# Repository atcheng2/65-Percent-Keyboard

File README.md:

# 65-Percent-Keyboard

QMK Based Keyboard based on the ATmega32A and the VUSB protocol. This build
implements an ANSI 65% layout for standard MX-style switches. The ATmega32A is
implemented over the more standard ATmega32u4 that has native USB support due to
budget constraints and part availability.

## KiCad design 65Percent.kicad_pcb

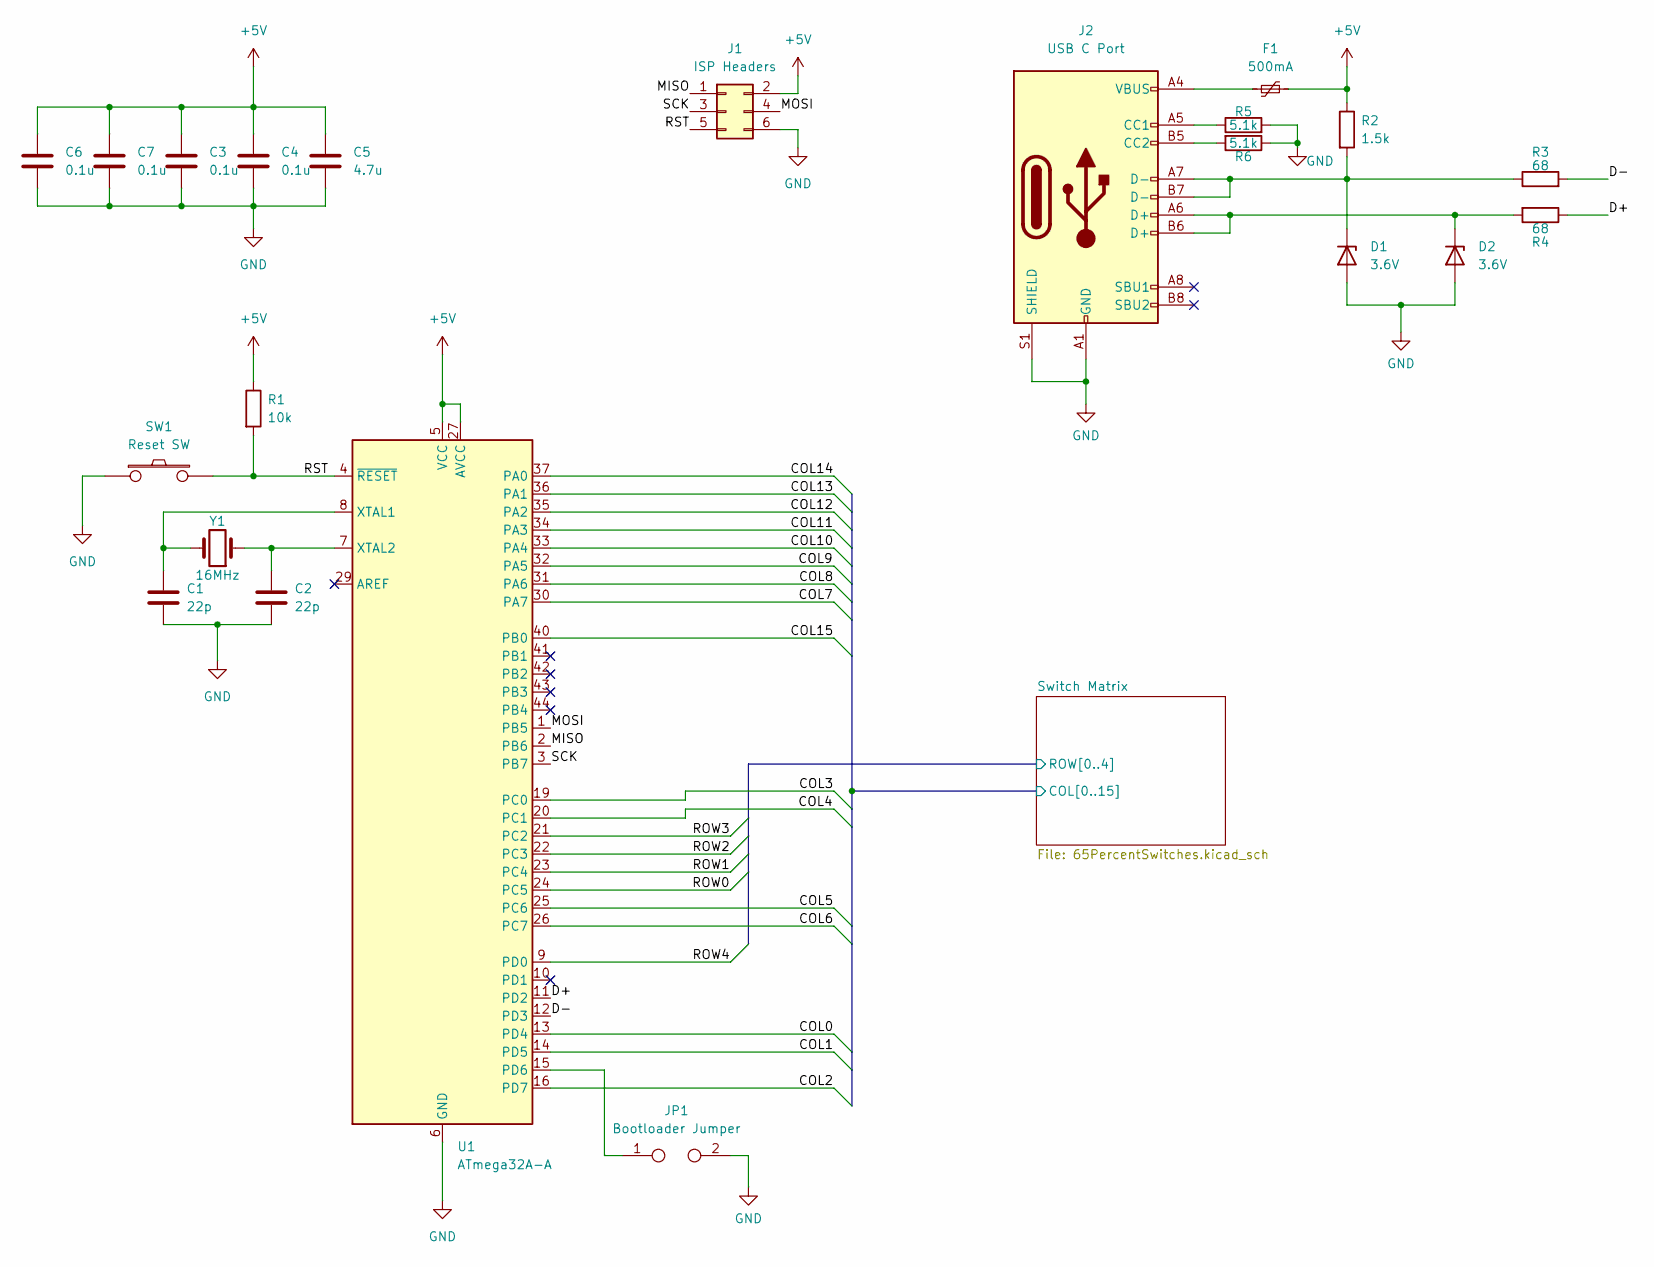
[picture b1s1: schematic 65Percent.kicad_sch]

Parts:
C1, C2: 22p; C_0805_2012Metric_Pad1.18x1.45mm_HandSolder
C3, C4, C6, C7: 0.1u; C_0805_2012Metric_Pad1.18x1.45mm_HandSolder
C5: 4.7u; C_0805_2012Metric_Pad1.18x1.45mm_HandSolder
D1, D2: 3.6V; D_DO-35_SOD27_P7.62mm_Horizontal
F1: 500mA; Fuse_0805_2012Metric_Pad1.15x1.40mm_HandSolder
J1: ISP Headers; PinHeader_2x03_P2.54mm_Vertical
J2: USB C Port; USB_C_2169900002
JP1: Bootloader Jumper; SOLDER_JUMPER_2
R1: 10k; R_0805_2012Metric_Pad1.20x1.40mm_HandSolder
R2: 1.5k; R_0805_2012Metric_Pad1.20x1.40mm_HandSolder
R3, R4: 68; R_0805_2012Metric_Pad1.20x1.40mm_HandSolder
R5, R6: 5.1k; R_0805_2012Metric_Pad1.20x1.40mm_HandSolder
SW1: Reset SW; Pushbutton_PTS526
U1: ATmega32A-A; TQFP-44_10x10mm_P0.8mm
Y1: 16MHz; Clock_THT

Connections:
+5V: C3.1, C4.1, C5.1, C6.1, C7.1, F1.2, J1.2, R1.1, R2.1, U1.5 (VCC), U1.17 (VCC), U1.27 (AVCC), U1.38 (VCC)
/D+: R4.1, U1.11 (PD2)
/D-: R3.2, U1.12 (PD3)
/MISO: J1.1, U1.2 (PB6)
/MOSI: J1.4, U1.1 (PB5)
/RST: J1.5, R1.2, SW1.2, U1.4 (~RESET)
/SCK: J1.3, U1.3 (PB7)
/Switch Matrix/COL0: U1.13 (PD4); also elsewhere on the board
/Switch Matrix/COL1: U1.14 (PD5); also elsewhere on the board
/Switch Matrix/COL2: U1.16 (PD7); also elsewhere on the board
/Switch Matrix/COL3: U1.19 (PC0); also elsewhere on the board
/Switch Matrix/COL4: U1.20 (PC1); also elsewhere on the board
/Switch Matrix/COL5: U1.25 (PC6); also elsewhere on the board
/Switch Matrix/COL6: U1.26 (PC7); also elsewhere on the board
/Switch Matrix/COL7: U1.30 (PA7); also elsewhere on the board
/Switch Matrix/COL8: U1.31 (PA6); also elsewhere on the board
/Switch Matrix/COL9: U1.32 (PA5); also elsewhere on the board
/Switch Matrix/COL10: U1.33 (PA4); also elsewhere on the board
/Switch Matrix/COL11: U1.34 (PA3); also elsewhere on the board
/Switch Matrix/COL12: U1.35 (PA2); also elsewhere on the board
/Switch Matrix/COL13: U1.36 (PA1); also elsewhere on the board
/Switch Matrix/COL14: U1.37 (PA0); also elsewhere on the board
/Switch Matrix/COL15: U1.40 (PB0); also elsewhere on the board
/Switch Matrix/ROW0: U1.24 (PC5); also elsewhere on the board
/Switch Matrix/ROW1: U1.23 (PC4); also elsewhere on the board
/Switch Matrix/ROW2: U1.22 (PC3); also elsewhere on the board
/Switch Matrix/ROW3: U1.21 (PC2); also elsewhere on the board
/Switch Matrix/ROW4: U1.9 (PD0); also elsewhere on the board
GND: C1.2, C2.2, C3.2, C4.2, C5.2, C6.2, C7.2, D1.2 (A), D2.2 (A), J1.6, J2.A1 (GND), J2.A12 (GND), J2.B1 (GND), J2.B12 (GND), J2.S1 (SHIELD), JP1.2, R5.2, R6.1, SW1.1, U1.6 (GND), U1.18 (GND), U1.28 (GND), U1.39 (GND)
unnamed: C1.1, U1.8 (XTAL1), Y1.2
unnamed: C2.1, U1.7 (XTAL2), Y1.1
unnamed: D1.1 (K), J2.A7 (D-), J2.B7 (D-), R2.2, R3.1
unnamed: D2.1 (K), J2.A6 (D+), J2.B6 (D+), R4.2
unnamed: F1.1, J2.A4 (VBUS), J2.A9 (VBUS), J2.B4 (VBUS), J2.B9 (VBUS)
unnamed: J2.A5 (CC1), R5.1
unnamed: J2.B5 (CC2), R6.2
unnamed: JP1.1, U1.15 (PD6)

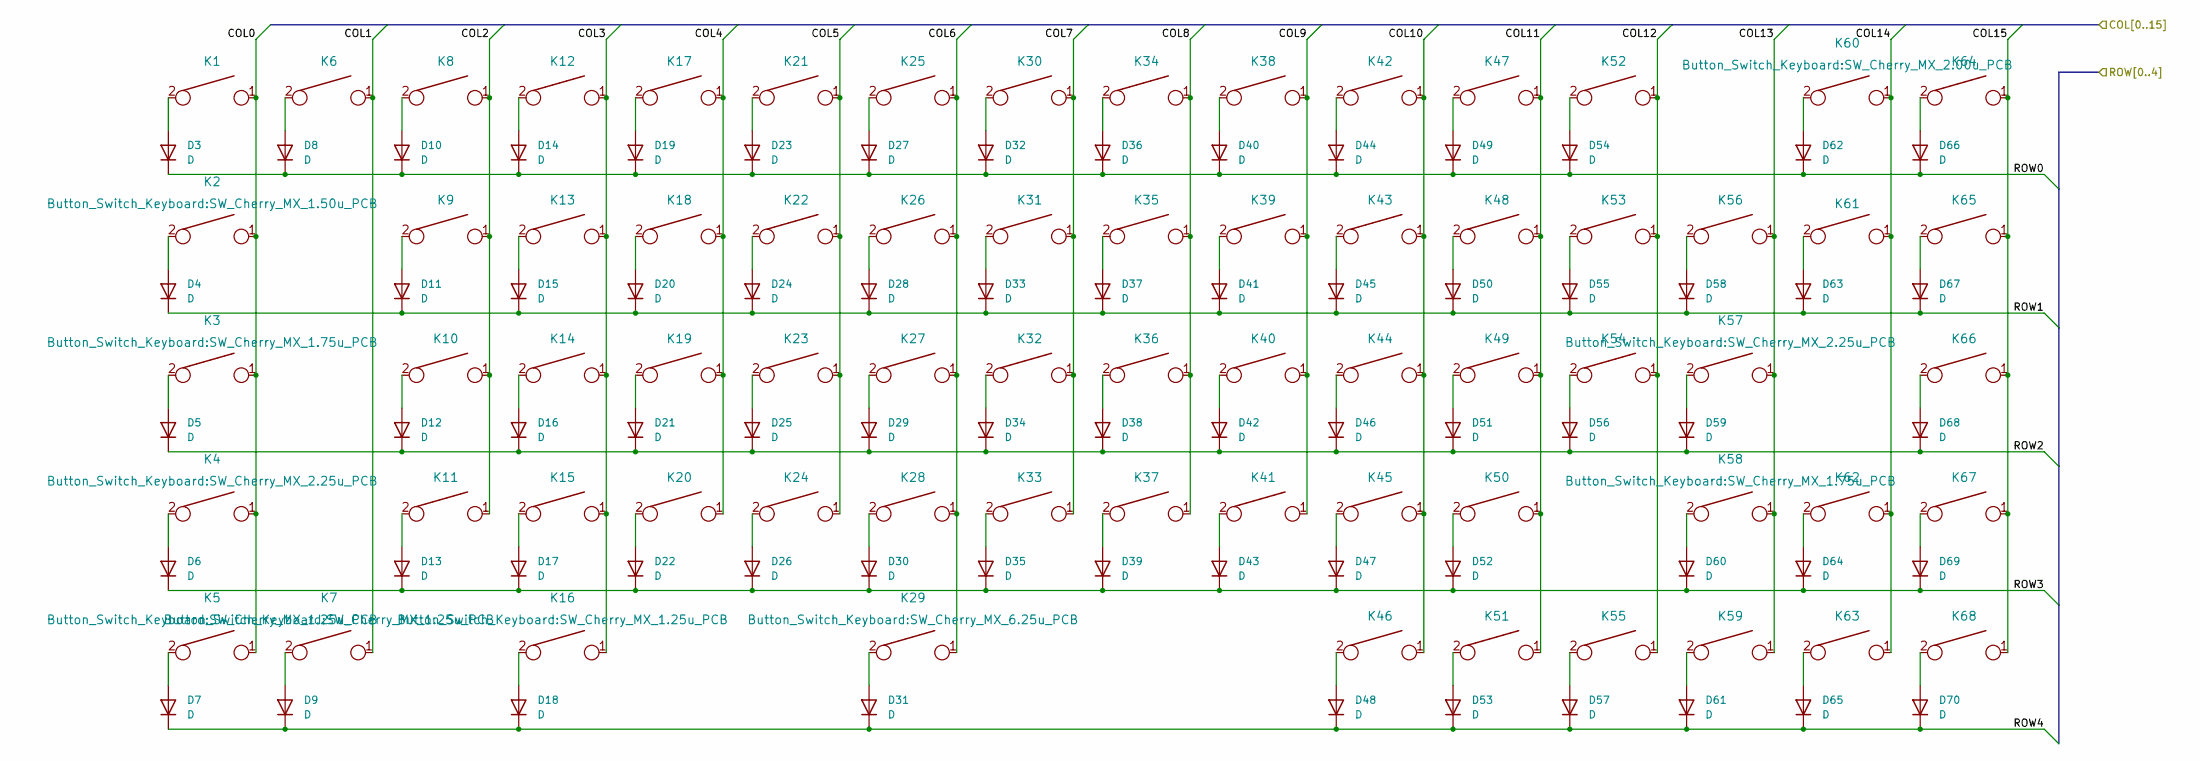
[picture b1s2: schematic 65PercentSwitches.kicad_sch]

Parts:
D3, D4, D5, D6, D7, D8, D9, D10, D11, D12, D13, D14, D15, D16, D17, D18, D19, D20, D21, D22, D23, D24, D25, D26, D27, D28, D29, D30, D31, D32, D33, D34, D35, D36, D37, D38, D39, D40, D41, D42, D43, D44, D45, D46, D47, D48, D49, D50, D51, D52, D53, D54, D55, D56, D57, D58, D59, D60, D61, D62, D63, D64, D65, D66, D67, D68, D69, D70: D; D_SOD123W_hand
K1, K6, K8, K9, K10, K11, K12, K13, K14, K15, K17, K18, K19, K20, K21, K22, K23, K24, K25, K26, K27, K28, K30, K31, K32, K33, K34, K35, K36, K37, K38, K39, K40, K41, K42, K43, K44, K45, K46, K47, K48, K49, K50, K51, K52, K53, K54, K55, K56, K59, K62, K63, K64, K65, K66, K67, K68: KEYSW; SW_Cherry_MX_1.00u_PCB
K2, K61: KEYSW; SW_Cherry_MX_1.50u_PCB
K3, K58: KEYSW; SW_Cherry_MX_1.75u_PCB
K4, K57: KEYSW; SW_Cherry_MX_2.25u_PCB
K5, K7, K16: KEYSW; SW_Cherry_MX_1.25u_PCB
K29: KEYSW; SW_Cherry_MX_6.25u_PCB
K60: KEYSW; SW_Cherry_MX_2.00u_PCB

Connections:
/Switch Matrix/COL0: K1.1, K2.1, K3.1, K4.1, K5.1; also elsewhere on the board
/Switch Matrix/COL1: K6.1, K7.1; also elsewhere on the board
/Switch Matrix/COL2: K8.1, K9.1, K10.1, K11.1; also elsewhere on the board
/Switch Matrix/COL3: K12.1, K13.1, K14.1, K15.1, K16.1; also elsewhere on the board
/Switch Matrix/COL4: K17.1, K18.1, K19.1, K20.1; also elsewhere on the board
/Switch Matrix/COL5: K21.1, K22.1, K23.1, K24.1; also elsewhere on the board
/Switch Matrix/COL6: K25.1, K26.1, K27.1, K28.1, K29.1; also elsewhere on the board
/Switch Matrix/COL7: K30.1, K31.1, K32.1, K33.1; also elsewhere on the board
/Switch Matrix/COL8: K34.1, K35.1, K36.1, K37.1; also elsewhere on the board
/Switch Matrix/COL9: K38.1, K39.1, K40.1, K41.1; also elsewhere on the board
/Switch Matrix/COL10: K42.1, K43.1, K44.1, K45.1, K46.1; also elsewhere on the board
/Switch Matrix/COL11: K47.1, K48.1, K49.1, K50.1, K51.1; also elsewhere on the board
/Switch Matrix/COL12: K52.1, K53.1, K54.1, K55.1; also elsewhere on the board
/Switch Matrix/COL13: K56.1, K57.1, K58.1, K59.1; also elsewhere on the board
/Switch Matrix/COL14: K60.1, K61.1, K62.1, K63.1; also elsewhere on the board
/Switch Matrix/COL15: K64.1, K65.1, K66.1, K67.1, K68.1; also elsewhere on the board
/Switch Matrix/ROW0: D3.1 (K), D8.1 (K), D10.1 (K), D14.1 (K), D19.1 (K), D23.1 (K), D27.1 (K), D32.1 (K), D36.1 (K), D40.1 (K), D44.1 (K), D49.1 (K), D54.1 (K), D62.1 (K), D66.1 (K); also elsewhere on the board
/Switch Matrix/ROW1: D4.1 (K), D11.1 (K), D15.1 (K), D20.1 (K), D24.1 (K), D28.1 (K), D33.1 (K), D37.1 (K), D41.1 (K), D45.1 (K), D50.1 (K), D55.1 (K), D58.1 (K), D63.1 (K), D67.1 (K); also elsewhere on the board
/Switch Matrix/ROW2: D5.1 (K), D12.1 (K), D16.1 (K), D21.1 (K), D25.1 (K), D29.1 (K), D34.1 (K), D38.1 (K), D42.1 (K), D46.1 (K), D51.1 (K), D56.1 (K), D59.1 (K), D68.1 (K); also elsewhere on the board
/Switch Matrix/ROW3: D6.1 (K), D13.1 (K), D17.1 (K), D22.1 (K), D26.1 (K), D30.1 (K), D35.1 (K), D39.1 (K), D43.1 (K), D47.1 (K), D52.1 (K), D60.1 (K), D64.1 (K), D69.1 (K); also elsewhere on the board
/Switch Matrix/ROW4: D7.1 (K), D9.1 (K), D18.1 (K), D31.1 (K), D48.1 (K), D53.1 (K), D57.1 (K), D61.1 (K), D65.1 (K), D70.1 (K); also elsewhere on the board
unnamed: D3.2 (A), K1.2
unnamed: D4.2 (A), K2.2
unnamed: D5.2 (A), K3.2
unnamed: D6.2 (A), K4.2
unnamed: D7.2 (A), K5.2
unnamed: D8.2 (A), K6.2
unnamed: D9.2 (A), K7.2
unnamed: D10.2 (A), K8.2
unnamed: D11.2 (A), K9.2
unnamed: D12.2 (A), K10.2
unnamed: D13.2 (A), K11.2
unnamed: D14.2 (A), K12.2
unnamed: D15.2 (A), K13.2
unnamed: D16.2 (A), K14.2
unnamed: D17.2 (A), K15.2
unnamed: D18.2 (A), K16.2
unnamed: D19.2 (A), K17.2
unnamed: D20.2 (A), K18.2
unnamed: D21.2 (A), K19.2
unnamed: D22.2 (A), K20.2
unnamed: D23.2 (A), K21.2
unnamed: D24.2 (A), K22.2
unnamed: D25.2 (A), K23.2
unnamed: D26.2 (A), K24.2
unnamed: D27.2 (A), K25.2
unnamed: D28.2 (A), K26.2
unnamed: D29.2 (A), K27.2
unnamed: D30.2 (A), K28.2
unnamed: D31.2 (A), K29.2
unnamed: D32.2 (A), K30.2
unnamed: D33.2 (A), K31.2
unnamed: D34.2 (A), K32.2
unnamed: D35.2 (A), K33.2
unnamed: D36.2 (A), K34.2
unnamed: D37.2 (A), K35.2
unnamed: D38.2 (A), K36.2
unnamed: D39.2 (A), K37.2
unnamed: D40.2 (A), K38.2
unnamed: D41.2 (A), K39.2
unnamed: D42.2 (A), K40.2
unnamed: D43.2 (A), K41.2
unnamed: D44.2 (A), K42.2
unnamed: D45.2 (A), K43.2
unnamed: D46.2 (A), K44.2
unnamed: D47.2 (A), K45.2
unnamed: D48.2 (A), K46.2
unnamed: D49.2 (A), K47.2
unnamed: D50.2 (A), K48.2
unnamed: D51.2 (A), K49.2
unnamed: D52.2 (A), K50.2
unnamed: D53.2 (A), K51.2
unnamed: D54.2 (A), K52.2
unnamed: D55.2 (A), K53.2
unnamed: D56.2 (A), K54.2
unnamed: D57.2 (A), K55.2
unnamed: D58.2 (A), K56.2
unnamed: D59.2 (A), K57.2
unnamed: D60.2 (A), K58.2
unnamed: D61.2 (A), K59.2
unnamed: D62.2 (A), K60.2
unnamed: D63.2 (A), K61.2
unnamed: D64.2 (A), K62.2
unnamed: D65.2 (A), K63.2
unnamed: D66.2 (A), K64.2
unnamed: D67.2 (A), K65.2
unnamed: D68.2 (A), K66.2
unnamed: D69.2 (A), K67.2
unnamed: D70.2 (A), K68.2

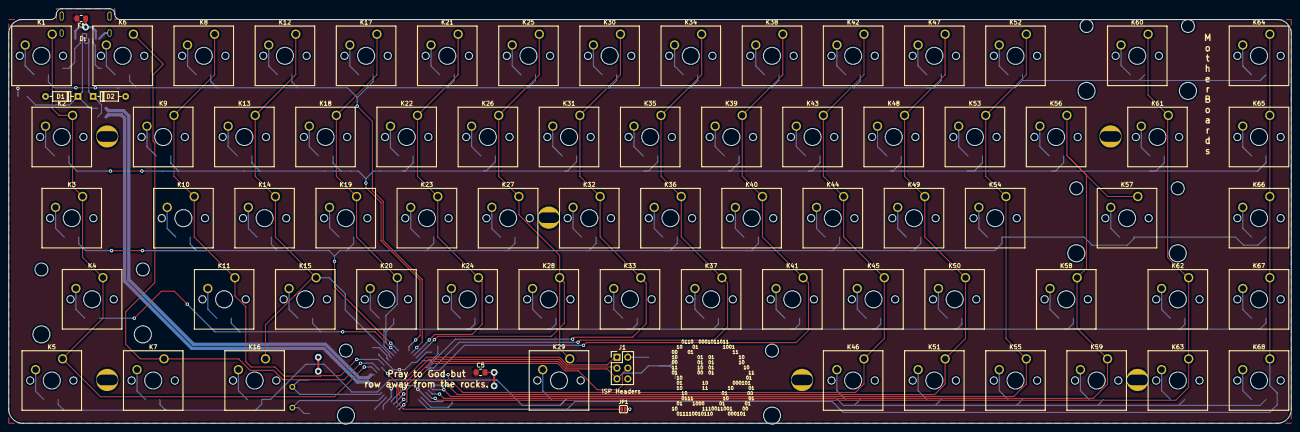
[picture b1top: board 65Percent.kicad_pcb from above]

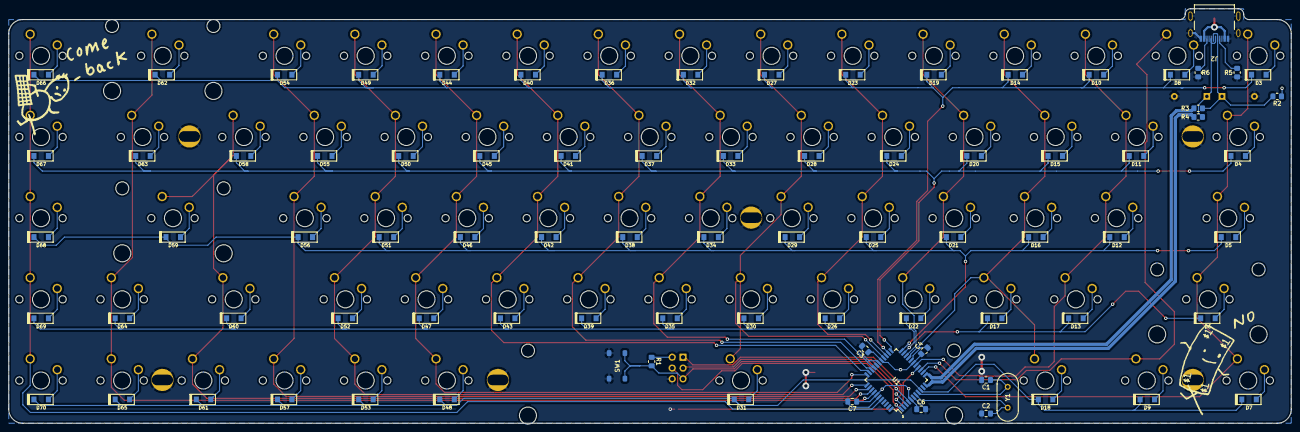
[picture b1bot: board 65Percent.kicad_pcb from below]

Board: 2 copper layers, 301.0 x 97.3 mm, 158 parts (84 on the bottom side), 105 nets.

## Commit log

2022-05-31 Initial commit, unrouted v1 of 65 Percent Keyboard
2022-05-31 Added fuses, column and diode wirings
2022-05-31 Completed first pass at v1 board
2022-09-05 Final V1 Board, Ordered
2023-08-29 Add files for flashing firmware
2023-08-29 Link in qmk_firmware
2023-08-29 Large file reorganization
2023-08-29 Fix flash makefile
2023-08-29 Add readme for flashing
2023-08-29 Add bootloaderconfig.h for completeness
2023-08-29 Update README.md
    Fix link to qmk
2023-08-29 Add pdfs of schematic and pcb
2023-08-29 Move pdfs and add image
2023-08-29 fix pdfs
